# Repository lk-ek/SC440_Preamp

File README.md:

# SC440 OPA1678 microphone preamp

## don't try this at home

Caveat: measurements show that the theoretical use for this preamp is a
reduction of the noise floor by a whopping 0.2dB. The noise seems to come from
either the capsule or the analog board.

So this is a nice flex mod as an exercise in analogue circuitry, but don't
expect any quality gains from it at all.

## Intro

A 5 V analog gain board for the **t.bone SC 440 USB microphone**. It sits between
its original microphone/JFET board and USB/ADC board, AC-couples the signal,
rebiases it around a buffered half-supply reference, and adds selectable gain.
The aim is to use less gain in the following ADC stage. A reduction in overall
recording noise depends on how much noise that stage contributes; microphone
and original analog-board noise are amplified along with the signal.

**Default in the current KiCad files:** amplifier gain +10.10 dB, using R8 = 2.2 kΩ and
R9 = 1 kΩ, with the C2 = 1 µF MLCC input option. C1, R1 and R2 are DNP.
C9 = 330 pF is populated across R8.

The board outline is **30 × 35 mm**, with 2 mm corner radii. PCB thickness in
this project is **1.6 mm**. Files were saved with **KiCad 10.99 nightly**; use a
build that supports their file format.

- [Assembly choices: gain and input capacitor](#assembly-choices)
- [Bill of materials](#bill-of-materials)
- [Connections and installation](#connections-and-installation)
- [Circuit and test points](#circuit-and-test-points)
- [Views](#views)
- [Simulation](#simulation)
- [Regenerating the README images](#regenerating-the-readme-images)

## Assembly choices

### Gain: approximately 6, 8 or 10 dB

The non-inverting amplifier uses `Av = 1 + R8/R9`, with R9 fixed at **1 kΩ**.
Populate one R8 value; these are alternatives, not additional resistors.

| Variant | R8 | R9 | Voltage gain | Gain | Concrete R8 example, Yageo thin film |
|---|---:|---:|---:|---:|---|
| 6 dB | 1 kΩ | 1 kΩ | 2.0× | +6.02 dB | `RT0805BRD071KL` |
| 8 dB | 1.5 kΩ | 1 kΩ | 2.5× | +7.96 dB | `RT0805BRD071K5L` |
| **10 dB — CAD default** | **2.2 kΩ** | **1 kΩ** | **3.2×** | **+10.10 dB** | `RT0805BRD072K2L` |

The table gives the amplifier gain. End-to-end gain from J2 pin 4 to J1 pin 4
is slightly lower: R4/R6 alone introduce about 0.086 dB attenuation. The
unloaded AC model gives approximately **5.93 / 7.87 / 10.01 dB at 1 kHz**
for the default MLCC option. See [SIMULATION_VALIDATION.md](SIMULATION_VALIDATION.md)
for both capacitor options and the 20 kHz results.

These parts are 0805, 0.1%, 25 ppm/°C, 0.125 W. Ordinary 1% resistors also work;
thin film is preferred for R8/R9 for ratio stability and low excess noise.
Thin film does not eliminate thermal noise. The lower resistance values reduce
that contribution compared with the older 22 kΩ/10 kΩ pair.

Use 6 dB where input-level headroom matters most; 10 dB provides the greatest
analog boost. For a fixed ADC clipping level, allowable microphone-board input
amplitude is inversely proportional to the selected voltage gain. Reduce ADC
gain to obtain comparable recording levels, then check loud speech and plosives.
An analog booster does not increase the ADC's full-scale voltage.

**C9 remains 330 pF for all three variants.** Its feedback-network pole is
approximately 482 kHz / 322 kHz / 219 kHz for 6 / 8 / 10 dB respectively. This
reduces the ideal amplifier gain toward unity at high frequencies; it is not a
filter whose gain falls to zero. Its calculated contribution at 20 kHz is only
about −0.006 / −0.014 / −0.032 dB respectively, before other circuit roll-off.

### Input coupling: MLCC or film

Choose exactly one of the following assemblies. The input resistor R4 and bias
resistor R6 are unchanged for either option.

| Part | **A — compact MLCC, CAD default** | **B — film** |
|---|---|---|
| C2 | **1 µF, 0805, X7R**, ≥16 V | **DNP** |
| C1 | DNP | **2.2 µF PET film**, Faratronic `C241J225J2SC000`, 63 V, 5 mm pitch |
| R1, R2 | DNP | **0 Ω each**, 0805 |
| R4 | 1 kΩ | 1 kΩ |
| R6 | 100 kΩ | 100 kΩ |
| Approximate input high-pass pole | 1.6 Hz | 0.72 Hz |

The default path is C2 → R4 → IN_AC. The film path is
R1 → C1 → R2 → R4 → IN_AC. Do not populate both coupling branches: the two
capacitors would operate in parallel rather than select a single option.

Both coupling capacitors are non-polarized. Film avoids the ferroelectric
voltage dependence and microphony of X7R, but takes more space. The MLCC option
is the compact assembly; its effective capacitance depends on the exact part
and bias. These differences do not by themselves establish an audible benefit
in the complete microphone.

The film variant requires assembly changes only. If editing KiCad to represent
that variant, mark C2 DNP and clear DNP on C1/R1/R2, then update the PCB from the
schematic. C1/R1/R2 are currently excluded from simulation as well, so changing
DNP flags alone is not sufficient to simulate the film path.

## Bill of materials

Quantities below are **per preamp PCB**. They describe the current electrical
values and footprints. Orderable examples are documented choices, not proof
that those exact manufacturers are already installed. Equivalent parts must
match value, dielectric/technology, package and mechanical clearance.

All SMD passives use **0805 hand-solder footprints**. Resistor examples are
0.125 W. No special “audio-grade” electrolytics are needed. Prices and stock
are intentionally not fixed in this BOM.

### Common parts for all six gain/capacitor combinations

| Ref. | Qty | Value / specification | Package / assembly side | Concrete part or ordering specification |
|---|---:|---|---|---|
| U1 | 1 | OPA1678 dual audio op-amp | SOIC-8, 3.9 × 4.9 mm, 1.27 mm pitch; front | **Texas Instruments `OPA1678IDR`**; do not substitute VSSOP/SON versions |
| R3 | 1 | 22 Ω, 1% | 0805; front | Yageo `RC0805FR-0722RL` |
| R4, R9 | 2 | 1 kΩ; thin film, 0.1% recommended | 0805; front | Yageo **`RT0805BRD071KL`**; thin film at R4 is optional |
| R5, R7 | 2 | 10 kΩ, 1% | 0805; front | Yageo `RC0805FR-0710KL` |
| R6 | 1 | 100 kΩ, 1% | 0805; front | Yageo `RC0805FR-07100KL` |
| R8 | 1 | **Select 1 kΩ / 1.5 kΩ / 2.2 kΩ** | 0805; front | Select exactly one part from the gain table above |
| R10 | 1 | 100 Ω, 1% | 0805; front | Yageo `RC0805FR-07100RL` |
| C3 | 1 | 47 µF, 16 V, ±20%, polarized | Radial, Ø5 × 11 mm, 2 mm pitch; front | **Aishi `ERS1CM470D11OT`**, [LCSC C160836](https://www.lcsc.com/product-detail/C160836.html), matching the schematic link |
| C4, C8 | 2 | 100 nF, X7R, ±10%, ≥16 V | 0805; **C4 front, C8 back** | Example: Murata `GRM21BR71H104KA01L`, 50 V |
| C5, C9 | 2 | 330 pF, **C0G/NP0**, ±5% | 0805; front | Example: Murata **`GRM2165C2A331JA01D`**, 100 V |
| C6 | 1 | 10 µF, 16 V, ±20%, polarized | Radial, Ø5 × 11 mm, 2 mm pitch; front, **mount lying down** | **Chengx `KM106M016D11RR0VH2FP0`**, [LCSC C43799](https://www.lcsc.com/product-detail/C43799.html), matching the schematic link |
| C7 | 1 | 1 nF, **C0G/NP0**, ±5% | 0805; front | Example: Murata **`GRM2165C2A102JA01D`**, 100 V |
| J1 | 1 | 4-pin JST XH header to digital board | **2.50 mm**, vertical/top-entry; back | **JST `B4B-XH-A`**; RoHS/tinning suffix may be shown as `(LF)(SN)` |
| J2 | 1 | 4-pin male header to analog board | **2.54 mm**, straight; back | 1×4, 0.64 mm square pins; cut from a standard strip; choose mating length to suit original socket and board spacing |
| TP1–TP5 | 5 PCB pads | Test pads, no purchased component required | 1 × 1 mm THT pad, 0.5 mm drill; front | Optional fine wire for probing; not five additional headers |

**C4 and C8 are required bypass capacitors and are included in the BOM.** Their
previous exclusion flags have been cleared in the root schematic, PCB and
synchronized AC schematic.

C3 alternative: **Rubycon `35ZLH47MEFC5X11`**, 47 µF / 35 V, Ø5 × 11 mm,
2 mm pitch, [LCSC C109390](https://www.lcsc.com/product-detail/C109390.html).
It fits the nominal pad pitch/body diameter and is electrically suitable;
ZLH is a low-impedance series, not a dedicated low-leakage series. The higher
voltage rating is not necessary here. Low leakage is useful at VREF_RAW, but a
standard good-quality aluminum electrolytic is sufficient for this application.

### Add parts for exactly one input option

| Variant | Ref. | Qty | Specification | Concrete example |
|---|---|---:|---|---|
| **A — MLCC** | C2 | 1 | 1 µF, X7R, ±10%, 0805, ≥16 V | Murata **`GRM219R71E105KA88D`**, 25 V |
| **B — film** | C1 | 1 | 2.2 µF, PET, ±5%, 63 V, 5 mm lead pitch | Faratronic **`C241J225J2SC000`**, [LCSC C5372007](https://www.lcsc.com/product-detail/C5372007.html) |
| **B — film** | R1, R2 | 2 | 0 Ω links, 0805 | Yageo **`RC0805JR-070RL`**, or suitable solder bridges |

The MLCC assembly has **14 SMD passives and two radial electrolytics**. The film
assembly has **15 SMD passives, two radial electrolytics and one film capacitor**.
Both also use U1, J1 and J2. Simulation sources and XREF1/XAMP1 are not physical
parts to order.

### Cable, original-board modification and mechanical supports

| Item | Qty per complete installation | Concrete choice / notes |
|---|---:|---|
| Additional digital-board header | 1 | JST **`B4B-XH-A`**, if replacing the original digital-board socket as described below; verify its hole spacing separately |
| Cable housings | 2 | JST **`XHP-4`**, 4 positions |
| Crimp contacts | 8 | JST **`SXH-001T-P0.6`**, for 22–28 AWG wire; use the matching crimp tooling, or a correctly wired premade XH cable |
| Cable conductors | 4 | Short flexible wires; verify pin-to-pin continuity rather than trusting wire colors |
| Replacement analog-board header | As required | Standard 2.54 mm 1×4 header; original connector relocation is part of the installation, not an extra gain-stage component |
| PCB-only support footprints | 2, optional mechanical population | Two back-side **1×2, 2.54 mm pin sockets**, currently both called `REF**`; their pads have **no electrical nets**. Select height to suit the original board or leave unpopulated if not needed for support |

Part references: [TI OPA1678 datasheet](https://www.ti.com/lit/ds/symlink/opa1678.pdf),
[JST XH datasheet](https://www.jst-mfg.com/product/pdf/eng/eXH.pdf),
[Yageo 2.2 kΩ RT specification](https://www.yageogroup.com/component-documentation/download/specsheet/RT0805BRD072K2L),
[Yageo 1.5 kΩ RT specification](https://www.yageogroup.com/component-documentation/download/specsheet/RT0805BRD071K5L),
[Yageo 1 kΩ RT specification](https://www.yageogroup.com/component-documentation/download/specsheet/RT0805BRD071KL),
[Murata MLCC catalog, including C0G parts](https://www.mouser.com/datasheet/2/281/murata_mure-s-a0000034126-1-1740300.pdf),
and [Murata 100 nF specification](https://search.murata.co.jp/Ceramy/image/img/A01X/G101/ENG/GRM21BR71H104KA01-01.pdf).
See [FOOTPRINT_CHECK.md](FOOTPRINT_CHECK.md) for the actual symbol/pad/device cross-check.

## Connections and installation

### Connector pinout

**J1 is the digital-board connector; J2 is the analog-board connector.** Both
are installed on the **back** of this PCB. The two pitches differ: JST XH is
2.50 mm, the unshrouded analog header is 2.54 mm.

| Pin number | J2 — from analog board | J1 — to digital board | Connection on this PCB |
|---|---|---|---|
| 1 | GND | GND | Direct common ground |
| 2 | LED | LED | Direct pass-through |
| 3 | +5V | +5V | Direct pass-through; preamp supply branches through R3 |
| 4 | ANALOG_INPUT | ANALOG_OUTPUT | Through coupling capacitor, amplifier and R10; **not** direct |

Use pad numbers, including the square pin-1 pad, rather than assuming a
left-to-right order from a photograph. Back-side placement and mirrored views
change the apparent order. Check the cable at both ends before connecting USB.

The intended installation mounts the daughterboard behind the original analog
PCB. Remove/reposition the original analog-board pin headers to the opposite
side to make the required board-to-board connection. Replace the original
digital-board pin socket with a JST XH header and use a short 4-wire cable to
J1. Verify actual original-board holes, mating parts and enclosure clearance
before final soldering; the daughterboard files do not define those original
board footprints.

**Keep the existing series DC-blocking capacitor on the digital-board audio
input.** J1 pin 4 carries the amplified AC signal on a DC level near VREF. There
is no output coupling capacitor on the daughterboard itself. The microphone's
exact ADC-side connection must be checked on the physical digital board.

C6 needs to be mounted **lying down** in the intended enclosure. Its CAD model
is a generic upright radial capacitor, so the 3D view is not the final assembly
orientation. Preserve polarity, avoid stressing the lead seals, and keep the
body/metalwork clear of exposed conductors. Check C3 and the optional C1 against
available height too. C1 currently has no attached 3D model.

## Circuit and test points

| Block | Actual parts / connections | Purpose / approximate behavior |
|---|---|---|
| Supply filter | R3 = 22 Ω; C6 = 10 µF and C8 = 100 nF from VCC_A to GND | Filters raw USB 5 V; ideal R3/C6 pole ≈723 Hz |
| Reference divider | R5 = 10 kΩ from VCC_A to VREF_RAW; R7 = 10 kΩ to GND; C3 = 47 µF and C4 = 100 nF to GND | Approximately VCC_A/2; divider/C3 pole ≈0.68 Hz |
| Reference buffer | U1B: pin 5 at VREF_RAW, pins 6/7 at VREF | Low-impedance reference for input bias and feedback |
| Input coupling / bias | C2 or C1/R1/R2; R4 = 1 kΩ; R6 = 100 kΩ to VREF | Blocks original-board DC and establishes the amplifier bias |
| Input RF filter | R4 with C5 = 330 pF from IN_AC to GND | Pole approximately 0.48 MHz for a low-impedance source; source impedance also matters |
| Amplifier | U1A; R8 from PREAMP_OUT to FB, R9 from FB to VREF | Gain selected by R8/R9 |
| Feedback HF shaping | C9 = 330 pF parallel to R8 | Gradually reduces gain toward unity above the feedback pole |
| Output isolation / filter | R10 = 100 Ω; C7 = 1 nF from ANALOG_OUTPUT to GND | Isolates capacitive cable/input load; ideal RC pole ≈1.59 MHz |

These pole calculations describe individual networks, not the complete loaded
frequency response. Cable/ADC loading and the op-amp's finite bandwidth also
contribute. Do not add a large capacitor directly to the buffered VREF output
without checking the buffer's capacitive-load stability; C3/C4 are on VREF_RAW.

| Test pad | Net | Expected DC with USB connected, no audio |
|---|---|---|
| TP1 | VCC_A | Raw +5V minus the drop across R3; **at least 4.5 V** for OPA1678 operation |
| TP2 | VREF_RAW | Approximately TP1/2 |
| TP3 | VREF | Approximately TP2 |
| TP4 | PREAMP_OUT | Approximately TP3 |
| TP5 | GND | Probe reference |

Raw USB voltage was reported above 4.9 V. At roughly 4.2 mA quiescent draw the
22 Ω resistor drops about 0.09 V; this is an estimate, not a minimum-voltage
measurement at the IC. Check TP1 under operation. The input signal is centered
near half supply; OPA1678 is not rail-to-rail at its inputs.

For commissioning, first check power and reference voltages, then compare
recordings at equal final level with reduced ADC gain. Check clipping with loud
speech/plosives and look for USB-related spurs. A valid rendering or simulated
trace does not replace those measurements.

## Views

The included images represent the saved default assembly (10 dB, MLCC).

### Schematic

### PCB layout — front

Copper, front silkscreen and board outline.

### PCB layout — back

Rear copper/silkscreen and board outline, mirrored as viewed from the back.

### 3D — front and back

DNP models are omitted. C6's generic upright model and C1's missing model mean
these images do not establish enclosure fit for every assembly variant.

## Simulation

There are two model paths. **Both schematics and both reference netlists now
use the current hardware topology and component references.** The AC project
was derived from the root schematic, with its AC-model properties, simulation
annotations and project metadata adapted.

| File / project | Status in this revision | Appropriate use |
|---|---|---|
| Root `SC440_Preamp.kicad_sch` + `.wbk` | Current root hardware values, including 2.2 kΩ/1 kΩ, R4/C5/C7/C9; default MLCC path | Transient / operating-point work after preparing the local TI model; not newly executed for this documentation update |
| `AC_SIM/SC440_Preamp_AC.kicad_sch` + `.wbk` | Current root topology; self-contained AC model; workbook plots output gain/phase | Current unloaded small-signal response for the default 10 dB / MLCC assembly |
| `SC440_Preamp_fallback.cir` | Current topology and references, including input/output filters and C9 | Transient fallback after preparing the TI model |
| `AC_SIM/SC440_Preamp_AC_reference.cir` | Current topology and references | Standalone AC analysis using the included model |

The root schematic uses a local ngspice adaptation of TI's **OPA167x TINA-TI
Spice Model (SBOMAC5D)**. Download it from the
[TI OPA1678 product page](https://www.ti.com/product/OPA1678), then run **from the
project root**:

```sh
python3 tools/prepare_ti_model.py ~/Downloads/sbomac5d.zip
```

This creates `vendor/OPA167x_ngspice.LIB`. The TI model is not shipped here.
The converter recognizes the documented Final 1.6 source hash; syntax adaptation
does not guarantee compatibility with every KiCad/ngspice version. The modified
noise and protection cells are not vendor-accurate. Treat the prepared model as
a simulation aid, not proof of measured noise or protection performance.

The AC model is project-authored and self-contained, with typical 114 dB
open-loop gain and 16 MHz GBW. It does not model clipping, slew, noise or rail
limits. Both AC files default to 10 dB / MLCC; change their R8/input assembly
when investigating other variants. Cable and ADC loading are not modeled. See
[SIMULATION_SPLIT.md](SIMULATION_SPLIT.md) and [AC_SIM/README.md](AC_SIM/README.md).
All six assembly variants were run with **ngspice 42** using the included AC
model. Results and validation limits are in
[SIMULATION_VALIDATION.md](SIMULATION_VALIDATION.md). Model setup details are in
[SIMULATION_MODEL.md](SIMULATION_MODEL.md).

## Regenerating the README images

Save schematic and PCB changes in KiCad first. The generator reads the saved
files, refills zones in a temporary PCB copy, exports each PCB side separately,
and renders the 3D component sides with KiCad's `top`/`bottom` views.

Install Python, Pillow and Inkscape. From the project root:

```sh
python3 -m venv .venv
source .venv/bin/activate
python -m pip install Pillow
python tools/regenerate_readme_images.py \
  --kicad-cli "/Applications/KiCad-nightly-260925/KiCad.app/Contents/MacOS/kicad-cli" \
  --inkscape "/Applications/Inkscape.app/Contents/MacOS/inkscape"
```

Those app paths are the current macOS example; adjust them for your installation.
The script can discover common app/PATH locations automatically. Use
`--models-dir PATH` if the installed 3D library cannot be resolved. It normally
rejects missing model files; `--allow-missing-models` explicitly allows incomplete
renders. DNP footprints' models are omitted automatically.

No KiCad source file is rewritten by the image generator. Images are staged and
validated before replacement. The old combined PCB image reference, if present,
is converted to front/back references in README.md only after successful exports.
For more detail on PCB views, override `--pcb-front-layers` and
`--pcb-back-layers`; fabrication/courtyard layers are omitted by default to keep
these views readable.

## Licensing and model redistribution

Project-authored content is **GPL-3.0-only**, except where separately noted:
[LICENSE.md](LICENSE.md), [LICENSES/GPL-3.0-only.txt](LICENSES/GPL-3.0-only.txt).
No TI SPICE macro-model is included or relicensed. See
[THIRD_PARTY_NOTICES.md](THIRD_PARTY_NOTICES.md) and [vendor/README.md](vendor/README.md).

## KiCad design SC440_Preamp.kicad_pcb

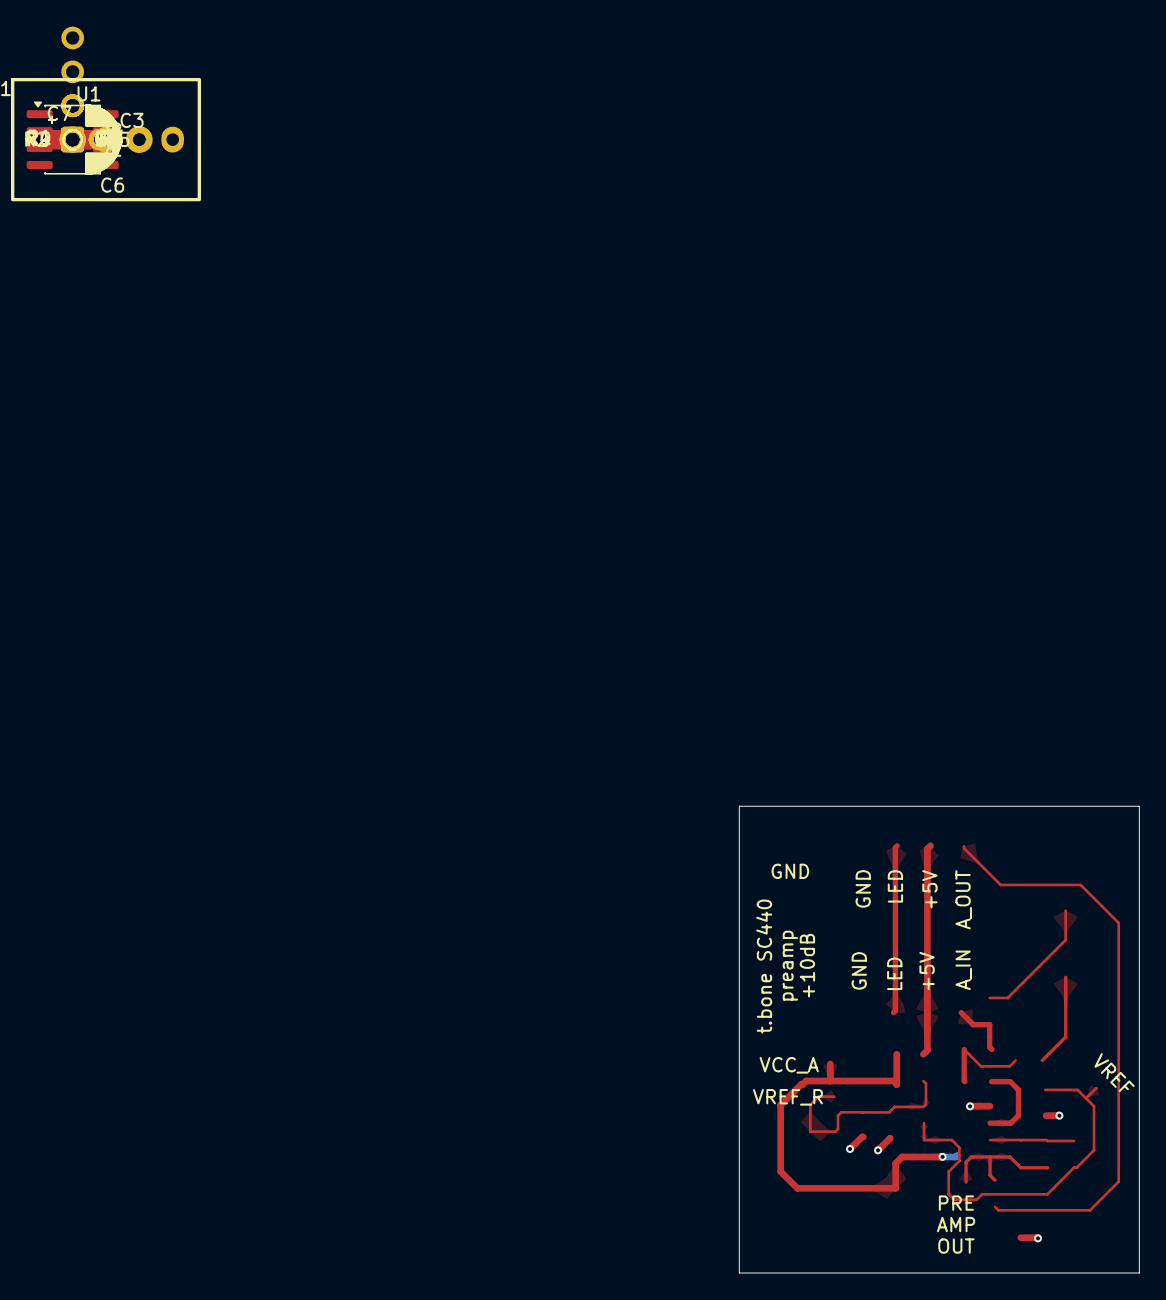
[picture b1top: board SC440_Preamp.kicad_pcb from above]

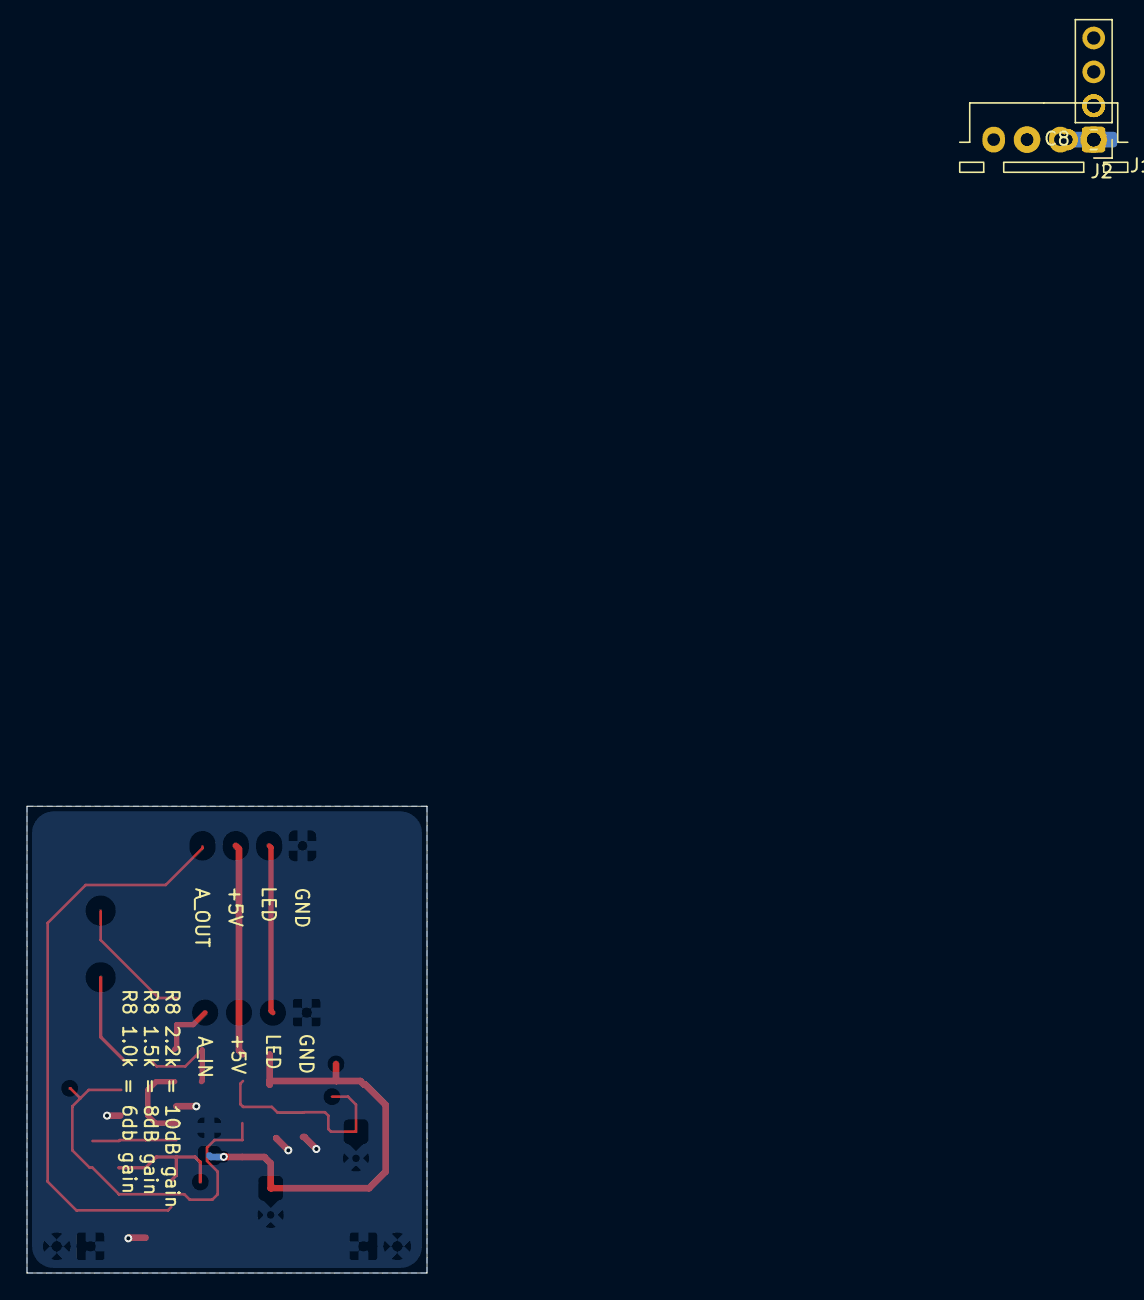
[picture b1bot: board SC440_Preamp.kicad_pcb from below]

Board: 2 copper layers, 30.0 x 35.0 mm, 27 parts (3 on the bottom side), 14 nets.

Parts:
C1: 2.2u; Faratronic_C241J225_P5.00mm
C2: 1u; C_0805_2012Metric_Pad1.18x1.45mm_HandSolder
C3: 47u; CP_Radial_D5.0mm_P2.00mm
C4, C8: 100n; C_0805_2012Metric_Pad1.18x1.45mm_HandSolder
C5, C9: 330p; C_0805_2012Metric_Pad1.18x1.45mm_HandSolder
C6: 10u; CP_Radial_D5.0mm_P2.00mm
C7: 1n; C_0805_2012Metric_Pad1.18x1.45mm_HandSolder
J1: JST-XH 1x04 TO DIGITAL BOARD; JST_XH_B4B-XH-A_1x04_P2.50mm_Vertical
J2: ANALOG BOARD; PinHeader_1x04_P2.54mm_Vertical
R1, R2: 0; R_0805_2012Metric_Pad1.20x1.40mm_HandSolder
R3: 22R; R_0805_2012Metric_Pad1.20x1.40mm_HandSolder
R4, R9: 1k; R_0805_2012Metric_Pad1.20x1.40mm_HandSolder
R5, R7: 10k; R_0805_2012Metric_Pad1.20x1.40mm_HandSolder
R6: 100k; R_0805_2012Metric_Pad1.20x1.40mm_HandSolder
R8: 2.2k; R_0805_2012Metric_Pad1.20x1.40mm_HandSolder
R10: 100R; R_0805_2012Metric_Pad1.20x1.40mm_HandSolder
TP1, TP2, TP3, TP4, TP5: TestPoint; TestPoint_THTPad_D1.0mm_Drill0.5mm
U1: OPA1678IDR; SOIC-8_3.9x4.9mm_P1.27mm

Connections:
+5V: J1.3 (+5V), J2.3 (+5V), R3.1
/ANALOG_INPUT: C2.1, J2.4 (OUT), R1.2
/ANALOG_OUTPUT: C7.1, J1.4 (IN), R10.2
/FB: C9.1, R8.1, R9.2, U1.2 (-A)
/IN_AC: C5.1, R4.2, R6.1, U1.3 (+A)
/LED: J1.2 (LED), J2.2 (LED)
/PREAMP_OUT: C9.2, R8.2, R10.1, TP4.1 (1_1), U1.1 (OUT_A)
/VCC_A: C6.1 (+), C8.1, R3.2, R5.2, TP1.1 (1_1), U1.8 (V+)
/VREF: R6.2, R9.1, TP3.1 (1_1), U1.6 (-B), U1.7 (OUT_B)
/VREF_RAW: C3.1 (+), C4.1, R5.1, R7.1, TP2.1 (1_1), U1.5 (+B)
GND: C3.2 (-), C4.2, C5.2, C6.2 (-), C7.2, C8.2, J1.1 (GND), J2.1 (GND), R7.2, TP5.1 (1_1), U1.4 (V-)
unnamed: C1.1, R1.1
unnamed: C1.2, R2.1
unnamed: C2.2, R2.2, R4.1
